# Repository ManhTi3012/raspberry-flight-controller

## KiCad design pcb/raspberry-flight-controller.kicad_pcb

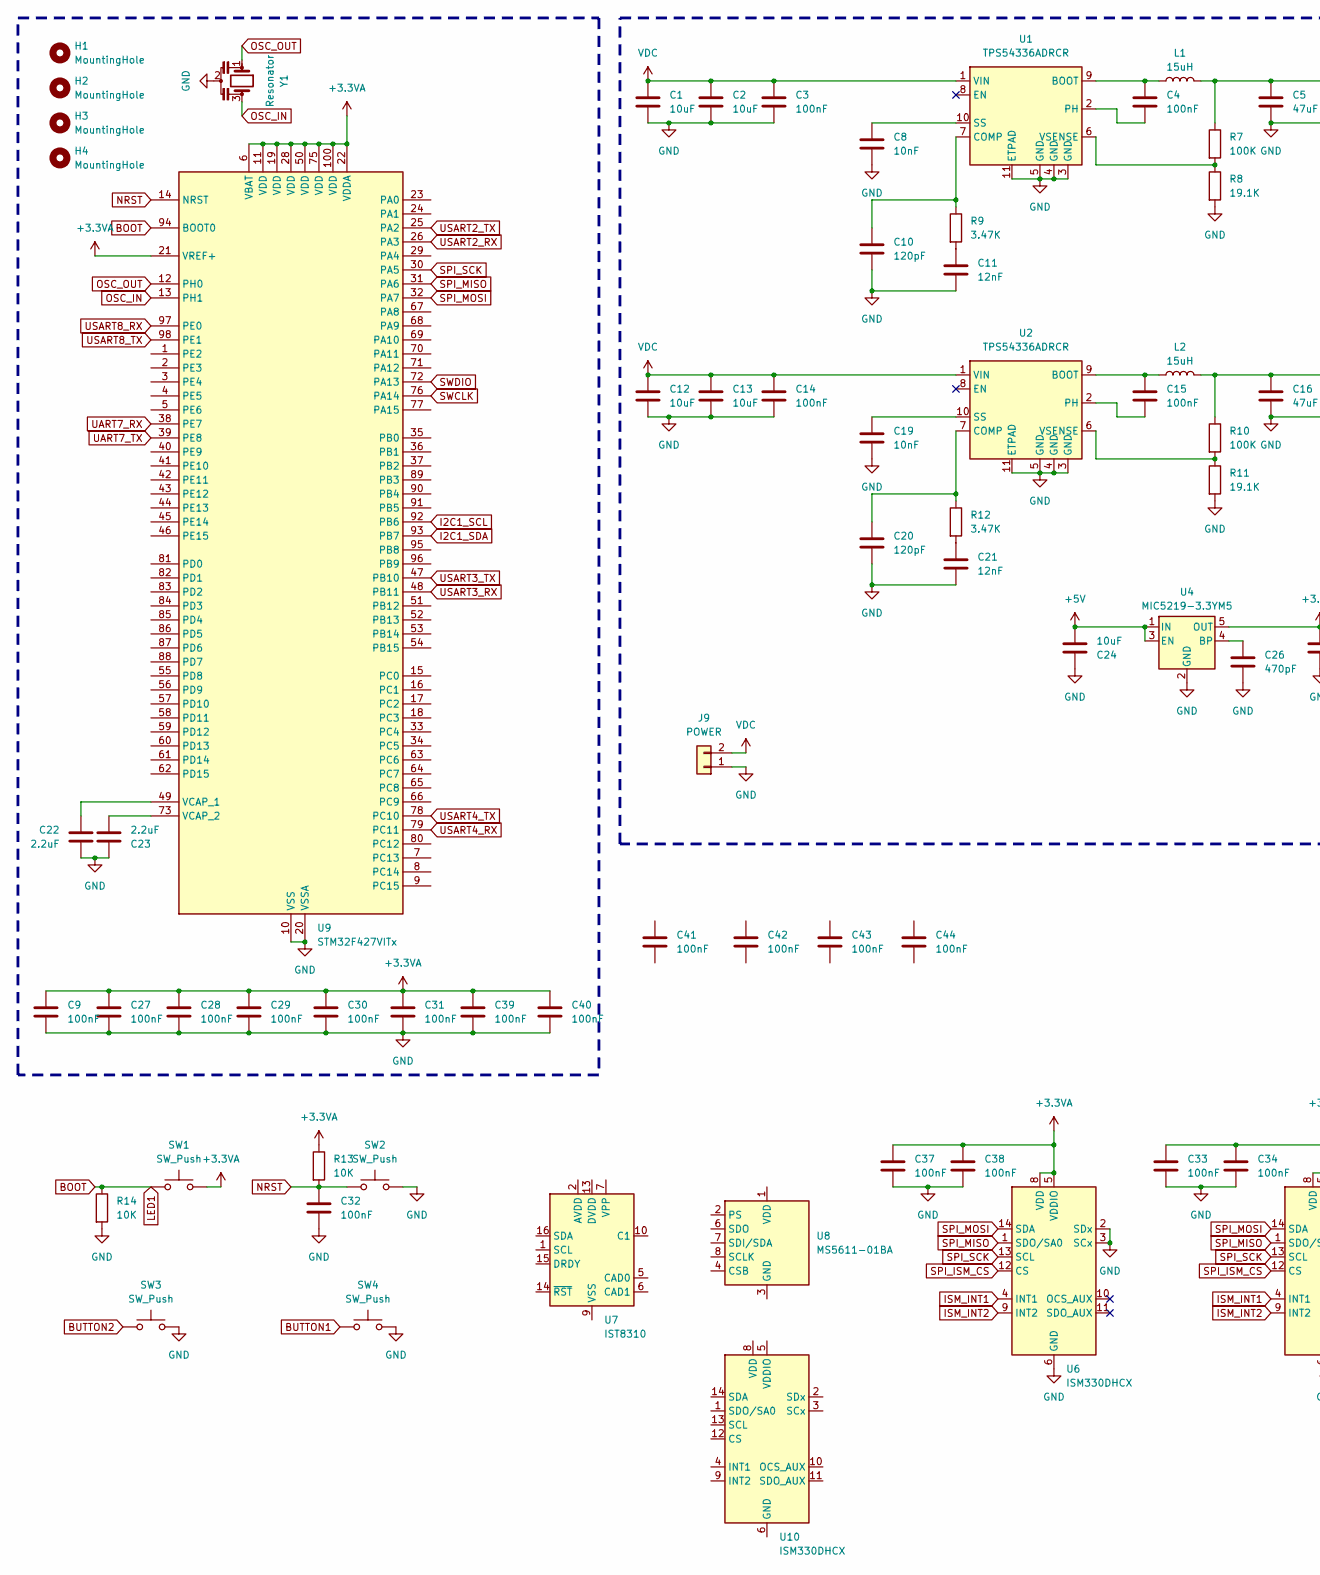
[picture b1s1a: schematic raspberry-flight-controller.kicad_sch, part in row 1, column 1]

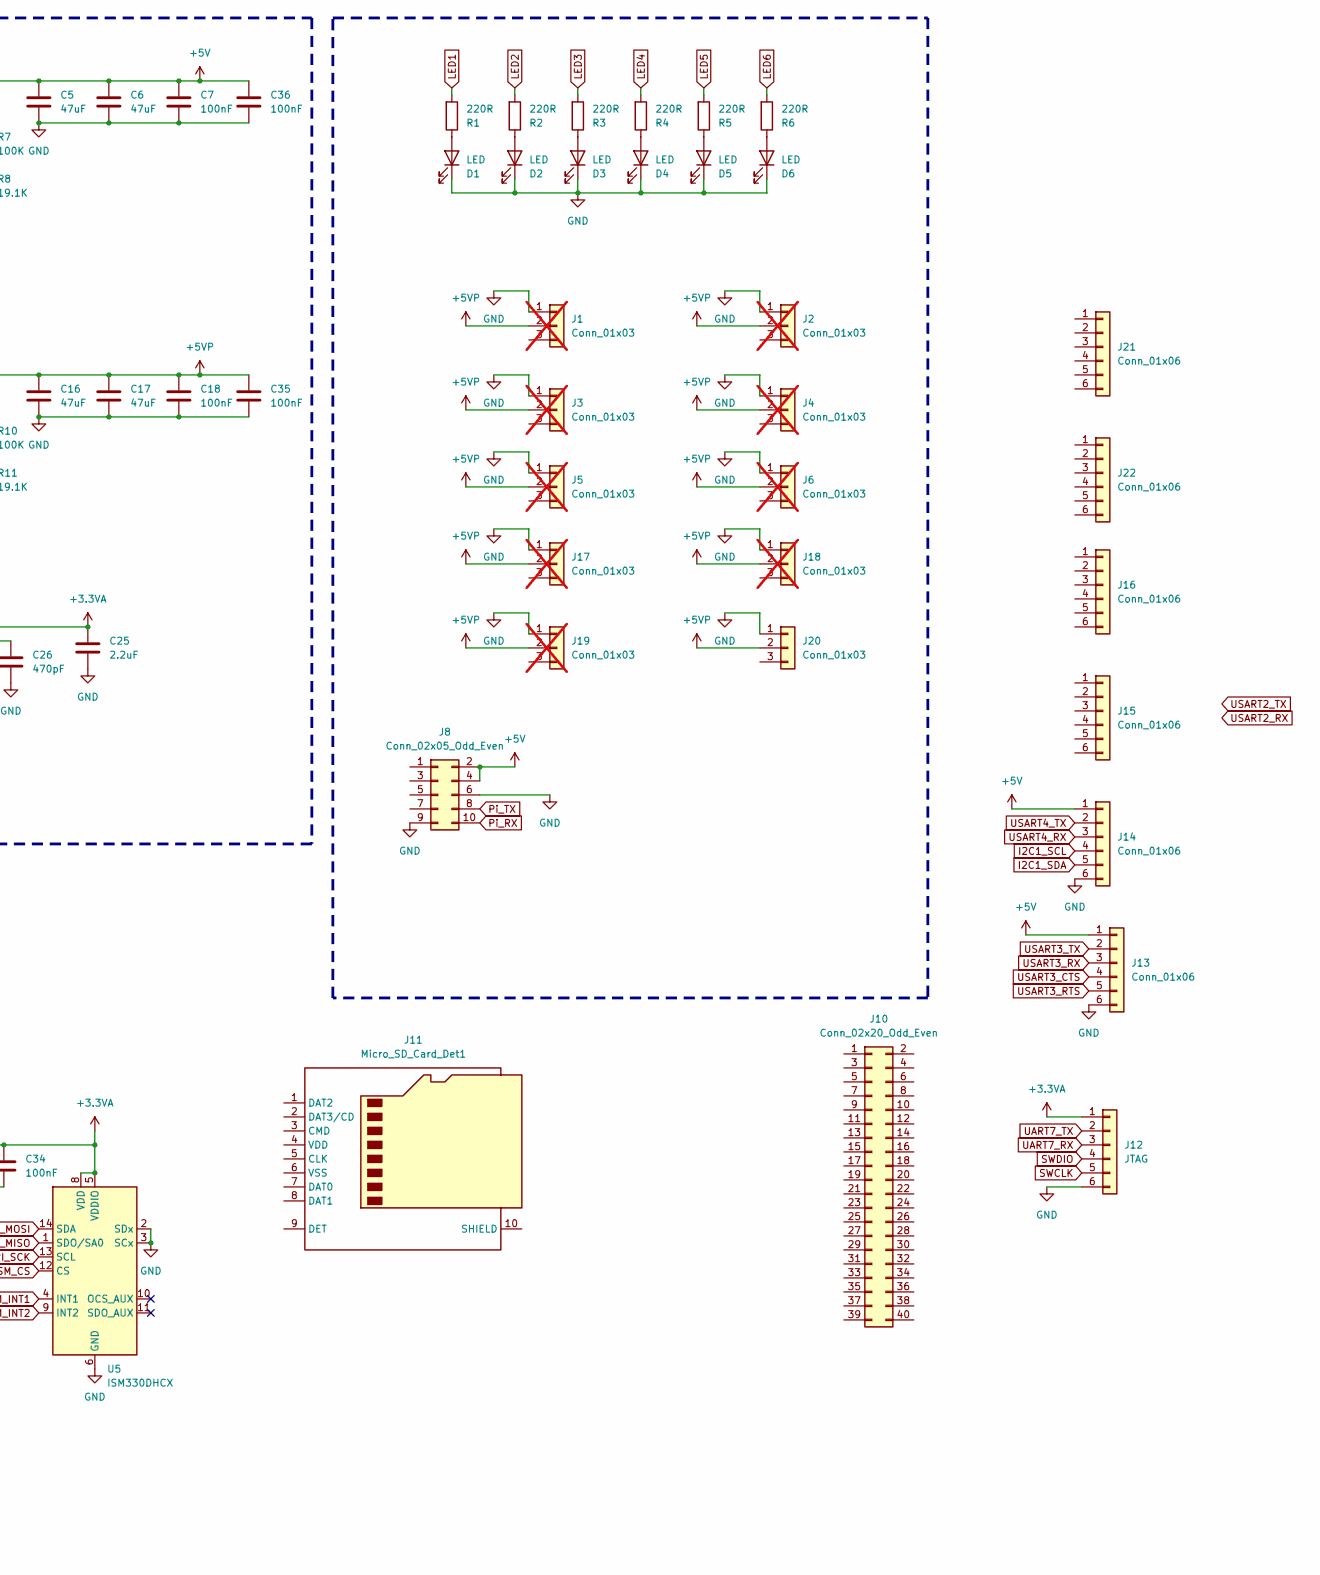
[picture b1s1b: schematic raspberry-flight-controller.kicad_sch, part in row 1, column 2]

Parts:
C1, C2, C12, C13: 10uF; C_1210_3225Metric
C3, C4, C7, C14, C15, C18, C33, C34, C35, C36, C37, C38, C41, C42, C43, C44: 100nF; C_0603_1608Metric
C5, C6, C16, C17: 47uF; C_1210_3225Metric
C8, C19: 10nF; C_0603_1608Metric
C9, C27, C28, C29, C30, C31, C32, C39, C40: 100nF; C_0402_1005Metric
C10, C20: 120pF; C_0603_1608Metric
C11, C21: 12nF; C_0603_1608Metric
C22, C23: 2.2uF; C_0402_1005Metric
C24: 10uF; C_0805_2012Metric
C25: 2.2uF; C_0805_2012Metric
C26: 470pF; C_0603_1608Metric
D1, D2, D3, D4, D5, D6: LED; LED_0603_1608Metric
H1, H2, H3, H4: MountingHole; MountingHole_2.7mm_M2.5
J1, J2, J3, J4, J5, J6, J17, J18, J19: Conn_01x03; PinHeader_1x03_P2.54mm_Vertical; not fitted
J8: Conn_02x05_Odd_Even; PinSocket_2x05_P2.54mm_Vertical
J9: POWER; DualPad_2x3mm
J10: Conn_02x20_Odd_Even; PinSocket_2x20_P2.54mm_Vertical
J11: Micro_SD_Card_Det1; microSD_HC_Molex_104031-0811
J12: JTAG; JST_SH_BM06B-SRSS-TB_1x06-1MP_P1.00mm_Vertical
J13, J14, J15, J16, J21, J22: Conn_01x06; JST_SH_BM06B-SRSS-TB_1x06-1MP_P1.00mm_Vertical
J20: Conn_01x03; PinHeader_1x03_P2.54mm_Vertical
L1, L2: 15uH; L_Bourns-SRN8040_8x8.15mm
R1, R2, R3, R4, R5, R6: 220R; R_0603_1608Metric
R7, R10: 100K; R_0603_1608Metric
R8, R11: 19.1K; R_0603_1608Metric
R9, R12: 3.47K; R_0603_1608Metric
R13, R14: 10K; R_0603_1608Metric
SW1, SW2, SW3, SW4: SW_Push; SW_SPST_B3U-1000P
U1, U2: TPS54336ADRCR; VSON-10-1EP_3x3mm_P0.5mm_EP1.65x2.4mm_ThermalVias
U4: MIC5219-3.3YM5; SOT-23-5
U5, U6, U10: ISM330DHCX; LGA-14_3x2.5mm_P0.5mm_LayoutBorder3x4y
U7: IST8310; LGA-16_3x3mm_P0.5mm
U8: MS5611-01BA; LGA-8_3x5mm_P1.25mm
U9: STM32F427VITx; LQFP-100_14x14mm_P0.5mm
Y1: Resonator; Resonator_SMD_Murata_CSTxExxV-3Pin_3.0x1.1mm

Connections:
+3.3VA: C9.1, C25.2, C27.1, C28.1, C29.1, C30.1, C31.1, C33.1, C34.1, C37.1, C38.1, C39.1, C40.1, J12.1, R13.1, SW1.2, U4.5 (OUT), U5.5 (VDDIO), U5.8 (VDD), U6.5 (VDDIO), U6.8 (VDD), U9.6 (VBAT), U9.11 (VDD), U9.19 (VDD), U9.21 (VREF+), U9.22 (VDDA), U9.28 (VDD), U9.50 (VDD), U9.75 (VDD), U9.100 (VDD)
+5V: C5.1, C6.1, C7.1, C24.1, C36.1, J8.2, J8.4, J13.1, J14.1, L1.2, R7.1, U4.1 (IN), U4.3 (EN)
+5VP: C16.1, C17.1, C18.1, C35.1, J1.2, J2.2, J3.2, J4.2, J5.2, J6.2, J17.2, J18.2, J19.2, J20.2, L2.2, R10.1
BOOT: R1.2, R14.1, SW1.1, U9.94 (BOOT0)
BUTTON1: SW4.1
BUTTON2: SW3.1
GND: C1.2, C2.2, C3.2, C5.2, C6.2, C7.2, C8.2, C9.2, C10.2, C11.2, C12.2, C13.2, C14.2, C16.2, C17.2, C18.2, C19.2, C20.2, C21.2, C22.1, C23.2, C24.2, C25.1, C26.1, C27.2, C28.2, C29.2, C30.2, C31.2, C32.1, C33.2, C34.2, C35.2, C36.2, C37.2, C38.2, C39.2, C40.2, D1.1 (K), D2.1 (K), D3.1 (K), D4.1 (K), D5.1 (K), D6.1 (K), J1.1, J2.1, J3.1, J4.1, J5.1, J6.1, J8.6, J8.9, J9.1, J12.6, J13.6, J14.6, J17.1, J18.1, J19.1, J20.1, R8.2, R11.2, R14.2, SW2.2, SW3.2, SW4.2, U1.3 (GND), U1.4 (GND), U1.5 (GND), U1.11 (ETPAD), U2.3 (GND), U2.4 (GND), U2.5 (GND), U2.11 (ETPAD), U4.2 (GND), U5.2 (SDx), U5.3 (SCx), U5.6 (GND), U5.7 (GND), U6.2 (SDx), U6.3 (SCx), U6.6 (GND), U6.7 (GND), U9.10 (VSS), U9.20 (VSSA), U9.27 (VSS), U9.74 (VSS), U9.99 (VSS), Y1.2
I2C1_SCL: J14.4, U9.92 (PB6)
I2C1_SDA: J14.5, U9.93 (PB7)
ISM_INT1: U5.4 (INT1), U6.4 (INT1)
ISM_INT2: U5.9 (INT2), U6.9 (INT2)
LED2: R2.2
LED3: R3.2
LED4: R4.2
LED5: R5.2
LED6: R6.2
NRST: C32.2, R13.2, SW2.1, U9.14 (NRST)
unnamed: C11.1, R9.2
unnamed: C21.1, R12.2
unnamed: D1.2 (A), R1.1
unnamed: D2.2 (A), R2.1
unnamed: D3.2 (A), R3.1
unnamed: D4.2 (A), R4.1
unnamed: D5.2 (A), R5.1
unnamed: D6.2 (A), R6.1
unnamed: C4.1, L1.1, U1.9 (BOOT)
unnamed: C10.1, R9.1, U1.7 (COMP)
unnamed: C4.2, U1.2 (PH)
unnamed: C8.1, U1.10 (SS)
unnamed: R7.2, R8.1, U1.6 (VSENSE)
unnamed: C15.1, L2.1, U2.9 (BOOT)
unnamed: C20.1, R12.1, U2.7 (COMP)
unnamed: C15.2, U2.2 (PH)
unnamed: C19.1, U2.10 (SS)
unnamed: R10.2, R11.1, U2.6 (VSENSE)
unnamed: C26.2, U4.4 (BP)
unnamed: U7.9 (VSS), U7.11 (VSS)
unnamed: U8.4 (CSB), U8.5 (CSB)
unnamed: C22.2, U9.49 (VCAP_1)
unnamed: C23.1, U9.73 (VCAP_2)
unnamed: U10.6 (GND), U10.7 (GND)
OSC_IN: U9.13 (PH1), Y1.3
OSC_OUT: U9.12 (PH0), Y1.1
Pi_RX: J8.10
Pi_TX: J8.8
SPI_ISM_CS: U5.12 (CS), U6.12 (CS)
SPI_MISO: U5.1 (SDO/SA0), U6.1 (SDO/SA0), U9.31 (PA6)
SPI_MOSI: U5.14 (SDA), U6.14 (SDA), U9.32 (PA7)
SPI_SCK: U5.13 (SCL), U6.13 (SCL), U9.30 (PA5)
SWCLK: J12.5, U9.76 (PA14)
SWDIO: J12.4, U9.72 (PA13)
UART7_RX: J12.3, U9.38 (PE7)
UART7_TX: J12.2, U9.39 (PE8)
USART2_RX: U9.26 (PA3)
USART2_TX: U9.25 (PA2)
USART3_CTS: J13.4
USART3_RTS: J13.5
USART3_RX: J13.3, U9.48 (PB11)
USART3_TX: J13.2, U9.47 (PB10)
USART4_RX: J14.3, U9.79 (PC11)
USART4_TX: J14.2, U9.78 (PC10)
USART8_RX: U9.97 (PE0)
USART8_TX: U9.98 (PE1)
VDC: C1.1, C2.1, C3.1, C12.1, C13.1, C14.1, J9.2, U1.1 (VIN), U2.1 (VIN)

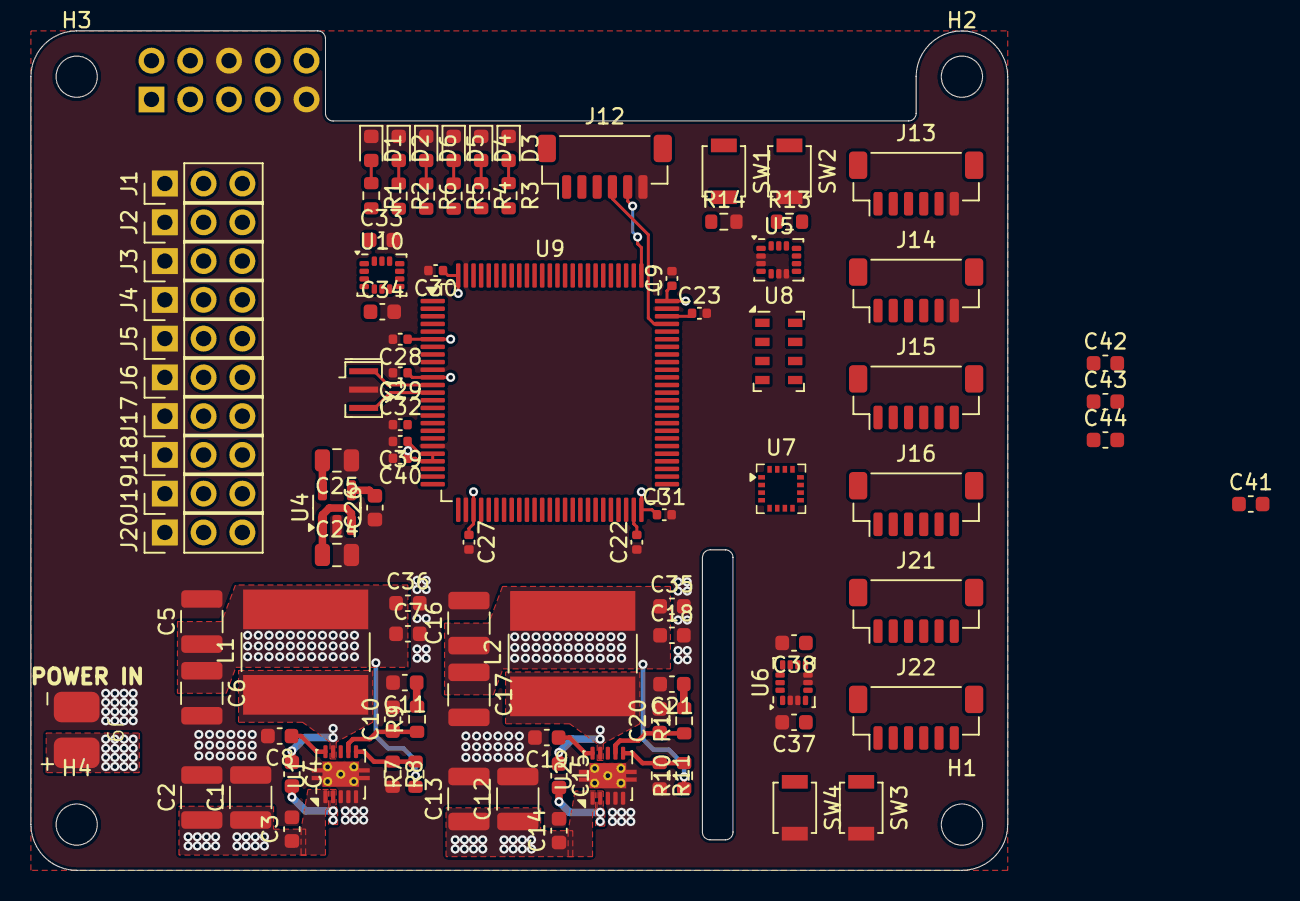
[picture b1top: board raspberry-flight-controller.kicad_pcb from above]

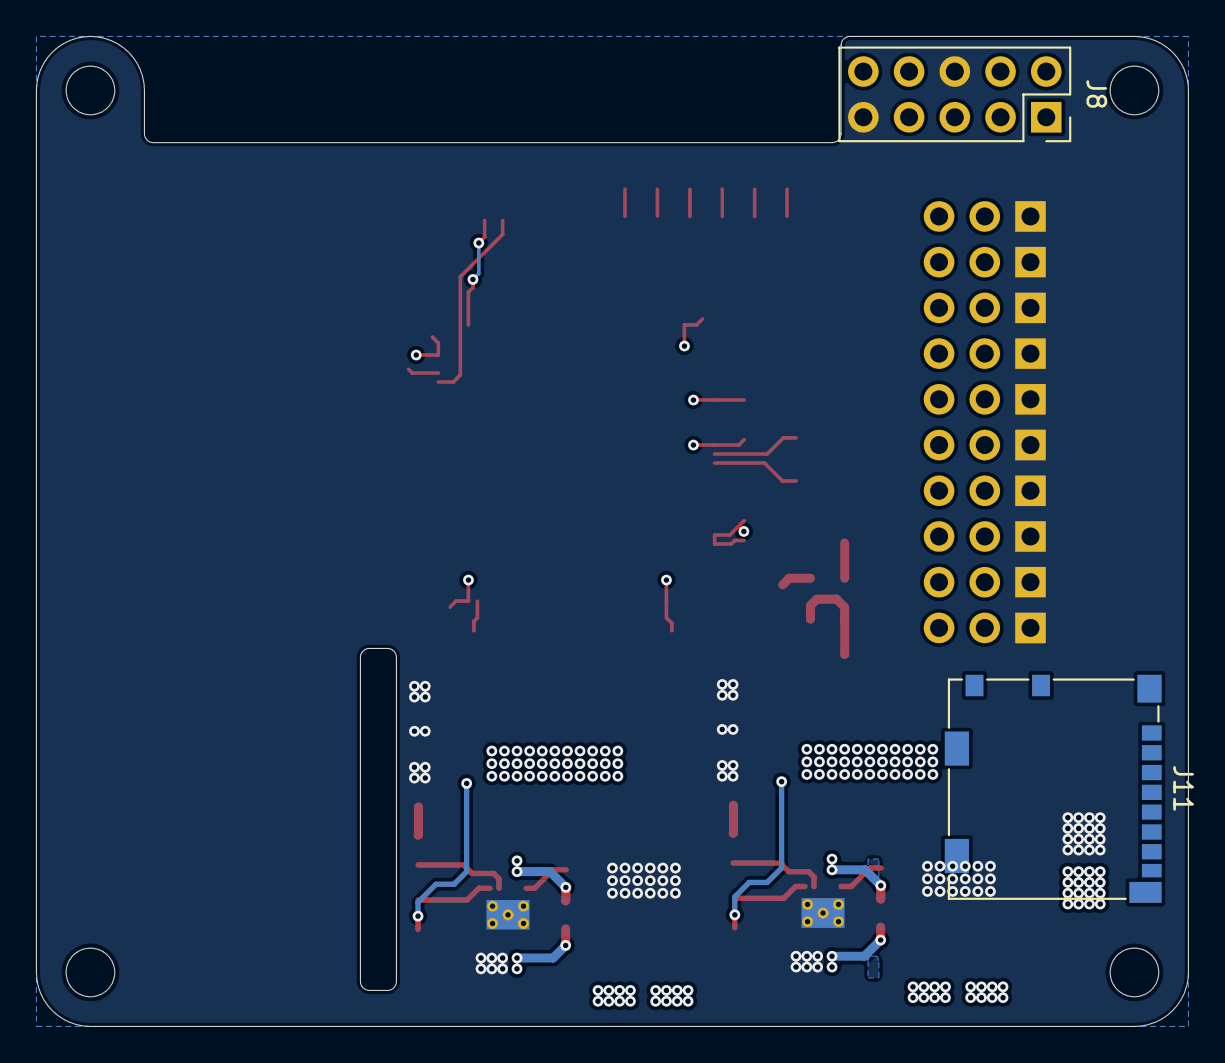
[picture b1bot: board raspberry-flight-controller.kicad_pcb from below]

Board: 4 copper layers, 64.0 x 55.0 mm, 104 parts (2 on the bottom side), 49 nets.

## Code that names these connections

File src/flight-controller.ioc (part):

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Mcu.Name=STM32F427V(G-I)Tx
Mcu.Package=LQFP100
Mcu.UserName=STM32F427VITx
PA10.Mode=Asynchronous
PA10.Signal=USART1_RX
PA11.Mode=CAN_Activate
PA11.Signal=CAN1_RX
PA12.Mode=CAN_Activate
PA12.Signal=CAN1_TX
PA13.Mode=Serial_Wire
PA13.Signal=SYS_JTMS-SWDIO
PA14.Mode=Serial_Wire
PA14.Signal=SYS_JTCK-SWCLK
PA2.Mode=Asynchronous
PA2.Signal=USART2_TX
PA3.Mode=Asynchronous
PA3.Signal=USART2_RX
PA5.Mode=Full_Duplex_Master
PA5.Signal=SPI1_SCK
PA6.Mode=Full_Duplex_Master
PA6.Signal=SPI1_MISO
PA7.Mode=Full_Duplex_Master
PA7.Signal=SPI1_MOSI
PA9.Mode=Asynchronous
PA9.Signal=USART1_TX
PB10.Mode=Asynchronous
PB10.Signal=USART3_TX
PB11.Mode=Asynchronous
PB11.Signal=USART3_RX
PB12.Mode=CAN_Activate
PB12.Signal=CAN2_RX
PB13.Mode=CAN_Activate
PB13.Signal=CAN2_TX
PB6.Mode=I2C
PB6.Signal=I2C1_SCL
PB7.Mode=I2C
PB7.Signal=I2C1_SDA
PC10.Mode=Asynchronous
PC10.Signal=UART4_TX
PC11.Mode=Asynchronous
PC11.Signal=UART4_RX
PC12.Mode=Asynchronous
PC12.Signal=UART5_TX
PD2.Mode=Asynchronous
PD2.Signal=UART5_RX
PE0.Mode=Asynchronous
PE0.Signal=UART8_RX
PE1.Mode=Asynchronous
PE1.Signal=UART8_TX
PE7.Mode=Asynchronous
PE7.Signal=UART7_RX
PE8.Mode=Asynchronous
PE8.Signal=UART7_TX
PH0/OSC_IN.Mode=HSE-External-Oscillator
PH0/OSC_IN.Signal=RCC_OSC_IN
PH1/OSC_OUT.Mode=HSE-External-Oscillator
PH1/OSC_OUT.Signal=RCC_OSC_OUT
RCC.HSE_VALUE=25000000
RCC.SYSCLKFreq_VALUE=16000000
board=custom

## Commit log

2025-09-21 Upload Files
2025-09-23 PCB update
